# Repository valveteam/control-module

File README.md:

# control-module
Control module for the valve

This repository contains;
* The Arduino code for flow control module
* A test file & I2C Scan program for debugging
* CAD File for the control module using an Arduino Micro as the Microcontroller
* CAD File for the control module using an Arduino Nano as the Microcontroller (Outdated)
 
## Notes
* The final design was implemented with the Micro so the CAD files are slightly outdated (the NMOS buffer circuits and additional trimmer not included)

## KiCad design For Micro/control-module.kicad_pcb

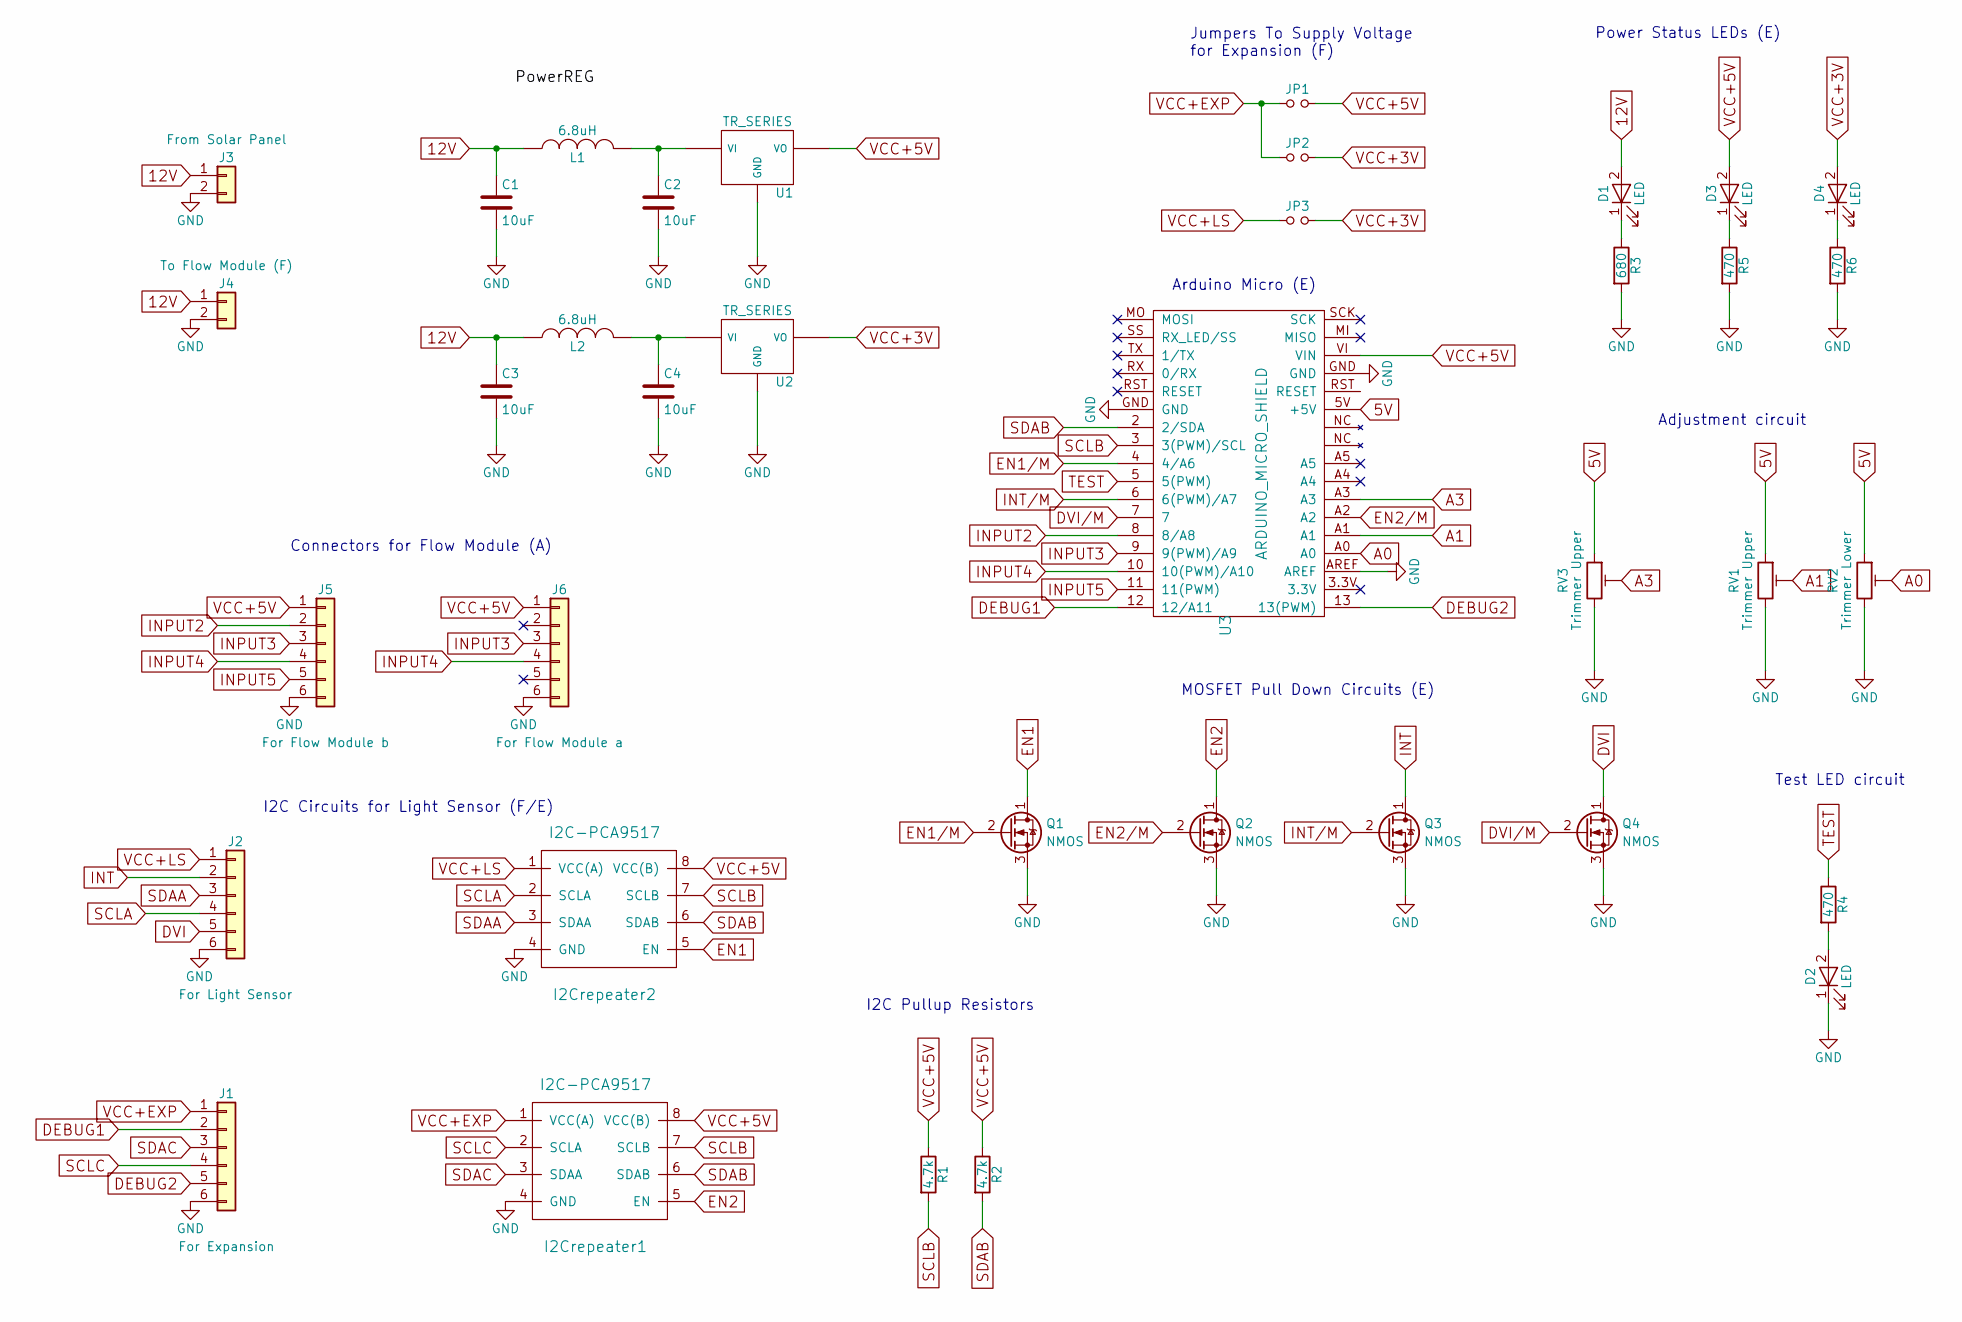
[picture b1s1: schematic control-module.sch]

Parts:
C1, C2, C3, C4: 10uF; C_0805_HandSoldering
D1, D2, D3, D4: LED; LED_0805_HandSoldering
I2Crepeater1, I2Crepeater2: I2C-PCA9517; TSSOP-8_3x3mm_Pitch0.65mm
J1: For Expansion; Molex_KK-6410-06_06x2.54mm_Straight
J2: For Light Sensor; Molex_KK-6410-06_06x2.54mm_Straight
J3: From Solar Panel; TE_TERM
J4: To Flow Module (F); TE_TERM
J5: For Flow Module b; Molex_KK-6410-06_06x2.54mm_Straight
J6: For Flow Module a; Molex_KK-6410-06_06x2.54mm_Straight
JP1, JP2, JP3: Jumper_NO_Small; SMD-solder-bridge
L1, L2: 6.8uH; WURTH_INDUCTOR
Q1, Q2, Q3, Q4: NMOS; SOT-23_Handsoldering
R1, R2: 4.7k; R_0805_HandSoldering
R3: 680; R_0805_HandSoldering
R4, R5, R6: 470; R_0805_HandSoldering
RV1, RV3: Trimmer Upper; Potentiometer_Trimmer_Vishay_T73XX_Vertical
RV2: Trimmer Lower; Potentiometer_Trimmer_Vishay_T73XX_Vertical
U1, U2: TR_SERIES; TR_Series
U3: ARDUINO_MICRO_SHIELD

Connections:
5V: RV1.1, RV2.1, RV3.1, U3.5V (+5V)
12V: C1.1, C3.1, D1.2 (A), J3.1, J4.1, L1.1, L2.1
A0: RV2.2, U3.A0
A1: RV1.2, U3.A1
A3: RV3.2, U3.A3
DEBUG1: J1.2, U3.12 (12/A11)
DEBUG2: J1.5, U3.13 (13(PWM))
DVI: J2.5, Q4.1 (D)
DVI/M: Q4.2 (G), U3.7
EN1: I2Crepeater2.5 (EN), Q1.1 (D)
EN1/M: Q1.2 (G), U3.4 (4/A6)
EN2: I2Crepeater1.5 (EN), Q2.1 (D)
EN2/M: Q2.2 (G), U3.A2
GND: C1.2, C2.2, C3.2, C4.2, D2.1 (K), I2Crepeater1.4 (GND), I2Crepeater2.4 (GND), J1.6, J2.6, J3.2, J4.2, J5.6, J6.6, Q1.3 (S), Q2.3 (S), Q3.3 (S), Q4.3 (S), R3.2, R5.2, R6.2, RV1.3, RV2.3, RV3.3, U1.GND, U2.GND, U3.AREF, U3.GND
INPUT2: J5.2, U3.8 (8/A8)
INPUT3: J5.3, J6.3, U3.9 (9(PWM)/A9)
INPUT4: J5.4, J6.4, U3.10 (10(PWM)/A10)
INPUT5: J5.5, U3.11 (11(PWM))
INT: J2.2, Q3.1 (D)
INT/M: Q3.2 (G), U3.6 (6(PWM)/A7)
unnamed: C2.1, L1.2, U1.VI
unnamed: C4.1, L2.2, U2.VI
unnamed: D1.1 (K), R3.1
unnamed: D2.2 (A), R4.2
unnamed: D3.1 (K), R5.1
unnamed: D4.1 (K), R6.1
SCLA: I2Crepeater2.2 (SCLA), J2.4
SCLB: I2Crepeater1.7 (SCLB), I2Crepeater2.7 (SCLB), R1.2, U3.3 (3(PWM)/SCL)
SCLC: I2Crepeater1.2 (SCLA), J1.4
SDAA: I2Crepeater2.3 (SDAA), J2.3
SDAB: I2Crepeater1.6 (SDAB), I2Crepeater2.6 (SDAB), R2.2, U3.2 (2/SDA)
SDAC: I2Crepeater1.3 (SDAA), J1.3
TEST: R4.1, U3.5 (5(PWM))
VCC+3V: D4.2 (A), JP2.2, JP3.2, U2.VO
VCC+5V: D3.2 (A), I2Crepeater1.8 (VCC(B)), I2Crepeater2.8 (VCC(B)), J5.1, J6.1, JP1.2, R1.1, R2.1, U1.VO, U3.VI (VIN)
VCC+EXP: I2Crepeater1.1 (VCC(A)), J1.1, JP1.1, JP2.1
VCC+LS: I2Crepeater2.1 (VCC(A)), J2.1, JP3.1

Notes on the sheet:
Adjustment circuit
Test LED circuit
I2C Circuits for Light Sensor (F/E)
Connectors for Flow Module (A)
Power Status LEDs (E)
MOSFET Pull Down Circuits (E)
I2C Pullup Resistors
Arduino Micro (E)
Jumpers To Supply Voltage for Expansion (F)

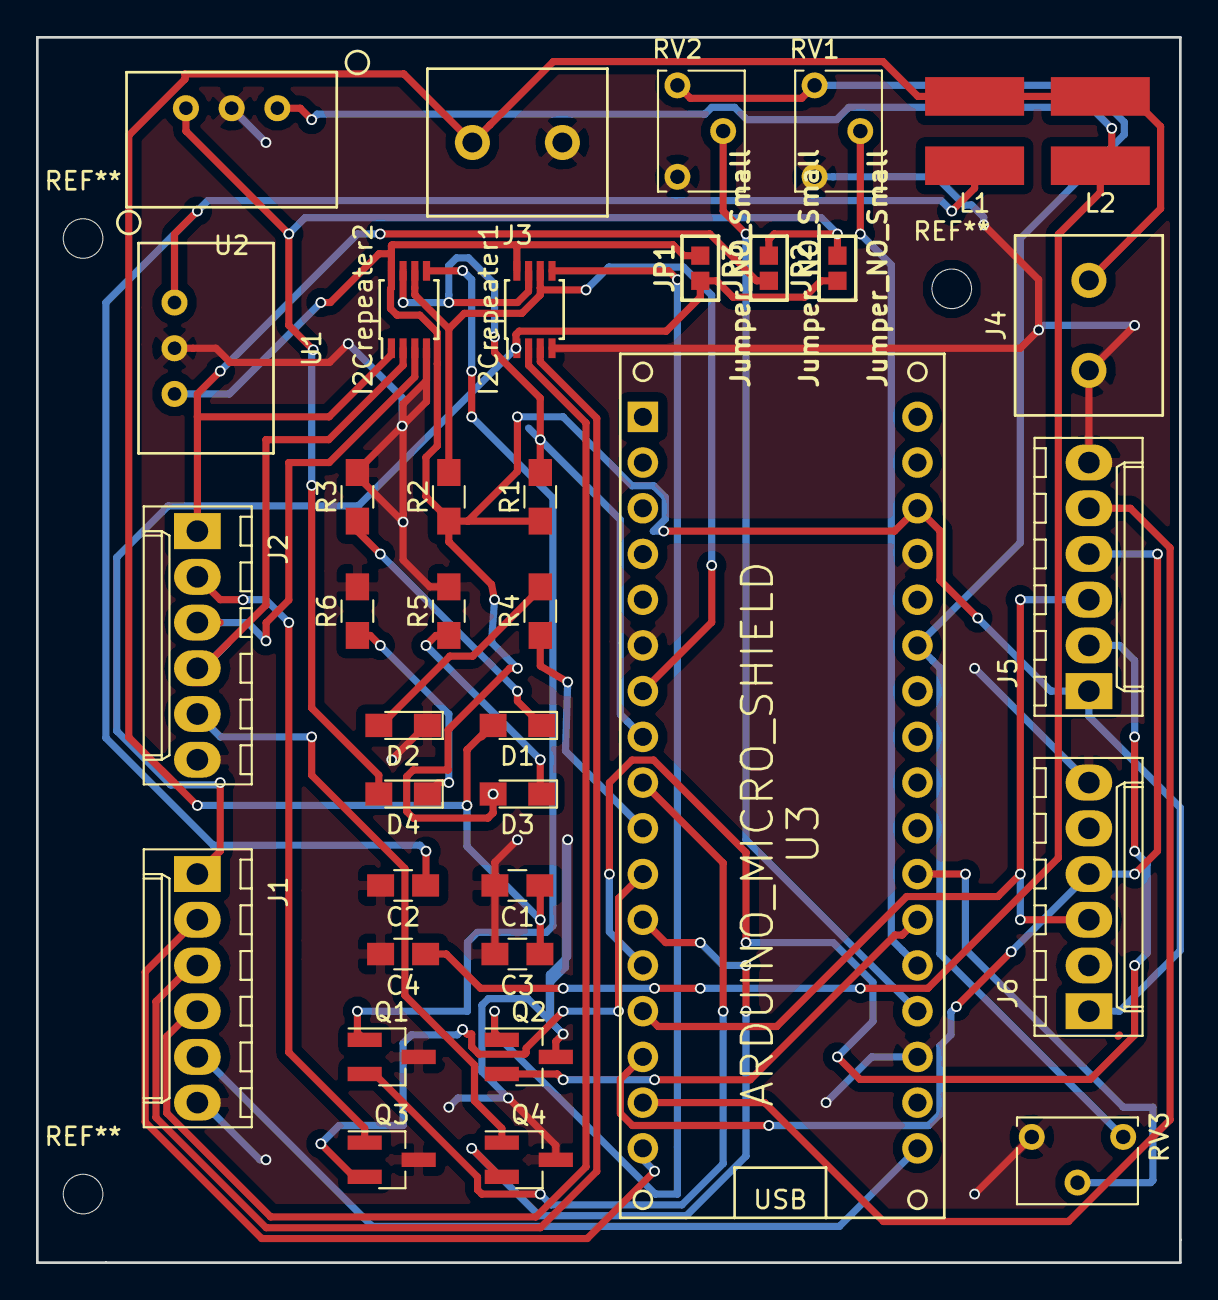
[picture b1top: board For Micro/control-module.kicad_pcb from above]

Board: 2 copper layers, 63.5 x 68.1 mm, 37 parts (0 on the bottom side), 37 nets.

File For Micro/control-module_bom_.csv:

Component,Description,Part,References,Value,Footprint,Quantity Per PCB,Datasheet
1,Unpolarized capacitor,C,C1 C2 C3 C4,10uF,C_0805_HandSoldering,4,
2,,LED-RESCUE-control-module,D1 D2 D3 D4,LED,LED_0805_HandSoldering,4,
3,,I2C-PCA9517,I2Crepeater1 I2Crepeater2,I2C-PCA9517,TSSOP-8_3x3mm_Pitch0.65mm,2,
4,"Generic connector, single row, 01x06",Conn_01x06,J1,For Expansion,Molex_KK-6410-06_06x2.54mm_Straight,1,
5,"Generic connector, single row, 01x06",Conn_01x06,J6,For Flow Module a,Molex_KK-6410-06_06x2.54mm_Straight,1,
6,"Generic connector, single row, 01x06",Conn_01x06,J5,For Flow Module b,Molex_KK-6410-06_06x2.54mm_Straight,1,
7,"Generic connector, single row, 01x06",Conn_01x06,J2,For Light Sensor,Molex_KK-6410-06_06x2.54mm_Straight,1,
8,"Generic connector, single row, 01x02",Conn_01x02,J3,From Solar Panel,TE_TERM,1,
9,"Generic connector, single row, 01x02",Conn_01x02,J4,To Flow Module (F),TE_TERM,1,
10,"Jumper, normally open",Jumper_NO_Small,JP1 JP2 JP3,Jumper_NO_Small,SMD-solder-bridge,3,
11,,INDUCTOR,L1 L2,6.8uH,WURTH_INDUCTOR,2,
12,Transistor N-MOSFET (general),Q_NMOS_DGS,Q1 Q2 Q3 Q4,NMOS,SOT-23_Handsoldering,4,
13,Resistor,R,R1 R2,4.7k,R_0805_HandSoldering,2,
14,Resistor,R,R4 R5 R6,470,R_0805_HandSoldering,3,
15,Resistor,R,R3,680,R_0805_HandSoldering,1,
16,Trim-Potentiometer,POT_TRIM,RV2,Trimmer Lower,Potentiometer_Trimmer_Vishay_T73XX_Vertical,1,
17,Trim-Potentiometer,POT_TRIM,RV1 RV3,Trimmer Upper,Potentiometer_Trimmer_Vishay_T73XX_Vertical,2,
18,Arduino Micro shield,ARDUINO_MICRO_SHIELD,U3,ARDUINO_MICRO_SHIELD,ARDUINO_MICRO_SHIELD,1,
19,Linear Regulator +5V,TR_SERIES,U1 U2,TR_SERIES,TR_Series,2,regulator\lm78xx.pdf





Component Groups:,19
Component Count:,37
Fitted Components:,37
Number of PCBs:,1
Total components:,37
Schematic Version:,
Schematic Date:,
BoM Date:,04/06/2018 09:44:44
Schematic Source:,C:/Users/tooyi/Dropbox/tfpb/control-module/For Micro/control-module.sch
KiCad Version:,Eeschema 4.0.7

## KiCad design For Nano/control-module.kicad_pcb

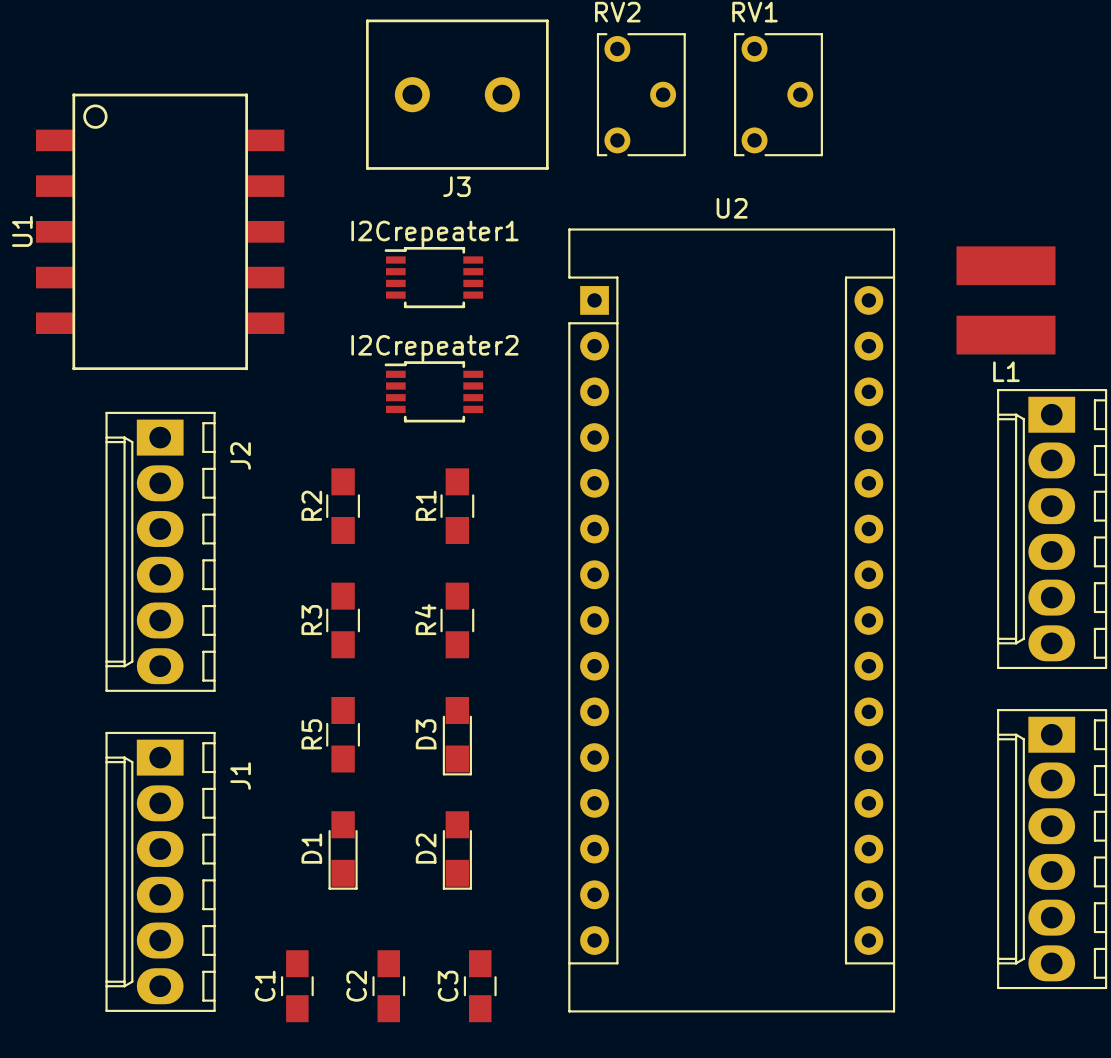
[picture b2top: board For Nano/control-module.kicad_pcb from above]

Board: 2 copper layers, 23 parts (0 on the bottom side), 22 nets, no tracks yet.

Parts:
C1, C2, C3: 4.7uF; C_0805_HandSoldering
D1, D2, D3: LED; LED_0805_HandSoldering
I2Crepeater1, I2Crepeater2: I2C-PCA9517; TSSOP-8_3x3mm_Pitch0.65mm
J1, J2: For Light Sensor; Molex_KK-6410-06_06x2.54mm_Straight
J3: From Solar Panel; TE_TERM
J4: For Flow Module b; Molex_KK-6410-06_06x2.54mm_Straight
J5: For Flow Module a; Molex_KK-6410-06_06x2.54mm_Straight
L1: 3.3uH; WURTH_INDUCTOR
R1, R2: 4.7k; R_0805_HandSoldering
R3: 680; R_0805_HandSoldering
R4, R5: 150; R_0805_HandSoldering
RV1: Trimmer Upper; Potentiometer_Trimmer_Vishay_T73XX_Vertical
RV2: Trimmer Lower; Potentiometer_Trimmer_Vishay_T73XX_Vertical
U1: STR05
U2: Arduino_Nano_R3; Arduino_Nano

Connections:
5V: RV1.1, RV2.1, U2.12
12V: C1.1, C2.1, J3.1, L1.1, R3.1
A0: RV2.2, U2.4
A1: RV1.2, U2.5
DEBUG1: J1.2, U2.17
DEBUG2: J1.5, U2.16
DVI: J2.5, U2.21
GND: C1.2, C2.2, C3.2, D1.1, D2.1, D3.1, J1.6, J2.6, J3.2, J4.6, J5.6, RV1.3, RV2.3, U1.GND, U2.3, U2.14, U2.19
INPUT2: J4.2, U2.26
INPUT3: J4.3, J5.3, U2.27
INPUT4: J4.4, J5.4, U2.28
INPUT5: J4.5, U2.29
INT: J2.2, U2.20
unnamed: D1.2, R3.2
unnamed: D2.2, R4.2
unnamed: D3.2, R5.2
unnamed: L1.2, U1.VI
SCLB: R1.2, U2.23
SDAB: R2.2, U2.22
TEST: R4.1, U2.1
VCC+3V: J1.1, J2.1
VCC+5V: J4.1, J5.1, R1.1, R2.1, R5.1, U1.VO, U2.15

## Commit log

2018-05-21 Adding files from personal git
2018-05-23 included I2c repeater
2018-05-23 First draft
2018-05-23 PCB Layout for Control Module
2018-05-25 Updated code for Arduino Micro
2018-05-26 Code with most functionality - not tested
    Added a "PWM" that changes value of tau from 0 - 1000, which would determine the proportion of time the valve is open.
    Using wikipedia, assumed upper bound to be around 20000 lux and lower bound to be around 1000 lux.
    Removed some bugs.
2018-05-27 Folder management and wrote code for VEML6030
    Successfully Compiled but not verified.
    Also, VEML returns uint_8 vs uint_16, have to dig into driver files to edit if more precision needed.
2018-05-28 removed bugs, set led to blink depending on signal
2018-05-28 Cleaned up control code, verified at this point. Added NMOS to Control CAD
2018-05-28 Test code
2018-05-28 Test circuit for solenoid and light
2018-05-28 added i2scan
2018-05-29 Add MOSFET circuits, power LED, regulator, connector and jumpers
2018-05-29 PCB for Control
2018-05-29 Update netlist and pcb with fixed I2C repeater
2018-05-30 CREATED README
2018-05-30 Final CAD for Micro
2018-05-30 Added pulse width adjustment
2018-05-30 Code Review
2018-05-31 Integrator and Debug Serial O/P added
2018-05-31 Added bounds for debug
2018-06-04 Bill of Materials
2018-06-04 crop
2018-06-06 Add file for the adapations for the LMD18201
